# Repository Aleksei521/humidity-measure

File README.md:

# humidity-measure
Moisture and temperature meter on PSOC 4200 and segment LCD
https://habr.com/ru/post/547644/#habracut

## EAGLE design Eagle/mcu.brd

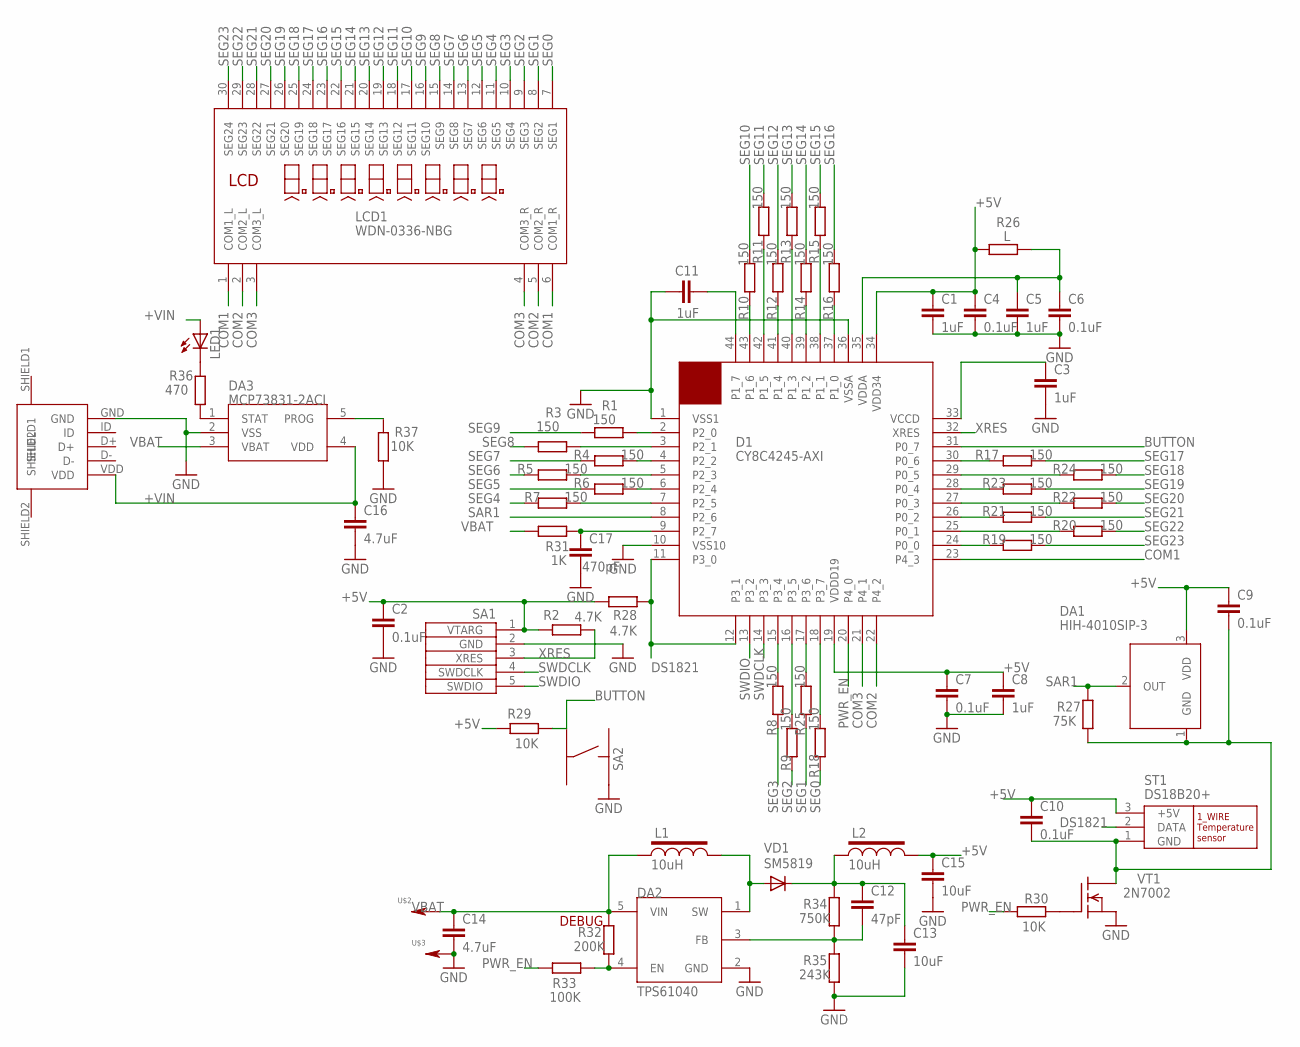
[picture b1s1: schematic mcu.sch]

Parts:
C1, C3, C5, C8, C11: 1uF; C0603
C2, C4, C6, C7, C9, C10: 0.1uF; C0603
C12: 47pF; C0805
C13, C15: 10uF; C0805
C14, C16: 4.7uF; C0805
C17: 470pF; C0603
D1: CY8C4245-AXI; TQFP44
DA1: HIH-4010SIP-3; SIP-3
DA2: TPS61040; SOT23-5L
DA3: MCP73831-2ACI; SOT23-5L
L1, L2: 10uH; SQC453226
LCD1: WDN-0336-NBG; WDN0336
LED1: LEDSMT1206; 1206
R1, R3, R4, R5, R6, R7, R8, R9, R10, R11, R12, R13, R14, R15, R16, R17, R18, R19, R20, R21, R22, R23, R24, R25: 150; R0603
R2, R28: 4.7K; R0603
R26: L; R0805
R27: 75K; R0603
R29, R30, R37: 10K; R0603
R31: 1K; R0603
R32: 200K; R0603
R33: 100K; R0603
R34: 750K; R0805
R35: 243K; R0805
R36: 470; R1206
SA1: SWDSWD-5; SWD-5
SA2: TACKT_BUTTONIIT-1102S; IIT-1102S
ST1: DS18B20+; TO92-
U$1: USB-MICRO; USB-MICRO-SMD
U$2: 1-PINHOME; 1-PIN_HOME
U$3: 1-PIN2_54; 1_PIN_2_54
VD1: SM5819; MELF-MLL41
VT1: 2N7002; SOT23

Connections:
+5V: C1.1, C2.1, C4.1, C7.1, C8.1, C9.1, C10.1, C15.1, D1.19 (VDDD19), D1.34 (VDD34), DA1.3 (VDD), L2.2 (L2), R2.2, R26.1, R28.2, R29.2, SA1.1 (VTARG), ST1.3 (+5V)
+VIN: C16.1, DA3.4 (VDD), LED1.A, U$1.VDD
BUTTON: D1.31 (P0_7), R29.1, SA2.SSR (2)
COM1: D1.23 (P4_3), LCD1.1 (COM1_L), LCD1.6 (COM1_R)
COM2: D1.22 (P4_2), LCD1.2 (COM2_L), LCD1.5 (COM2_R)
COM3: D1.21 (P4_1), LCD1.3 (COM3_L), LCD1.4 (COM3_R)
DS1821: D1.11 (P3_0), D1.12 (P3_1), R28.1, ST1.2 (DATA)
GND: C1.2, C2.2, C3.2, C4.2, C5.2, C6.2, C7.2, C8.2, C11.1, C13.2, C14.2, C15.2, C16.2, C17.2, D1.1 (VSS1), D1.10 (VSS10), D1.36 (VSSA), DA2.2 (GND), DA3.2 (VSS), R35.1, R37.1, SA1.2 (GND), SA2.SL (3), U$1.GND, U$3.P$1, VT1.2 (S)
unnamed: D1.2 (P2_0), R1.2
unnamed: D1.4 (P2_2), R4.2
unnamed: D1.6 (P2_4), R6.2
unnamed: D1.15 (P3_4), R8.2
unnamed: D1.3 (P2_1), R3.2
unnamed: D1.5 (P2_3), R5.2
unnamed: D1.7 (P2_5), R7.2
unnamed: D1.43 (P1_6), R10.1
unnamed: C3.1, D1.33 (VCCD)
unnamed: D1.42 (P1_5), R11.1
unnamed: D1.41 (P1_4), R12.1
unnamed: C5.1, C6.1, D1.35 (VDDA), R26.2
unnamed: D1.40 (P1_3), R13.1
unnamed: D1.39 (P1_2), R14.1
unnamed: D1.38 (P1_1), R15.1
unnamed: D1.37 (P1_0), R16.1
unnamed: D1.30 (P0_6), R17.1
unnamed: D1.29 (P0_5), R24.1
unnamed: D1.28 (P0_4), R23.1
unnamed: D1.16 (P3_5), R9.2
unnamed: D1.17 (P3_6), R25.2
unnamed: D1.18 (P3_7), R18.2
unnamed: D1.27 (P0_3), R22.1
unnamed: D1.26 (P0_2), R21.1
unnamed: D1.25 (P0_1), R20.1
unnamed: D1.24 (P0_0), R19.1
unnamed: C11.2, D1.44 (P1_7)
unnamed: C9.2, C10.2, DA1.1 (GND), R27.1, ST1.1 (GND), VT1.3 (D)
unnamed: R30.2, VT1.1 (G)
unnamed: C12.2, DA2.3 (FB), R34.1, R35.2
unnamed: DA2.4 (EN), R32.1, R33.2
unnamed: DA2.1 (SW), L1.2 (L2), VD1.A
unnamed: C12.1, C13.1, L2.1 (L1), R34.2, VD1.C
unnamed: DA3.1 (STAT), R36.1
unnamed: LED1.C, R36.2
unnamed: DA3.5 (PROG), R37.2
PWR_EN: D1.20 (P4_0), R30.1, R33.1
SAR1: D1.8 (P2_6), DA1.2 (OUT), R27.2
SAR2: C17.1, D1.9 (P2_7), R31.2
SEG0: LCD1.7 (SEG1), R18.1
SEG1: LCD1.8 (SEG2), R25.1
SEG2: LCD1.9 (SEG3), R9.1
SEG3: LCD1.10 (SEG4), R8.1
SEG4: LCD1.11 (SEG5), R7.1
SEG5: LCD1.12 (SEG6), R6.1
SEG6: LCD1.13 (SEG7), R5.1
SEG7: LCD1.14 (SEG8), R4.1
SEG8: LCD1.15 (SEG9), R3.1
SEG9: LCD1.16 (SEG10), R1.1
SEG10: LCD1.17 (SEG11), R10.2
SEG11: LCD1.18 (SEG12), R11.2
SEG12: LCD1.19 (SEG13), R12.2
SEG13: LCD1.20 (SEG14), R13.2
SEG14: LCD1.21 (SEG15), R14.2
SEG15: LCD1.22 (SEG16), R15.2
SEG16: LCD1.23 (SEG17), R16.2
SEG17: LCD1.24 (SEG18), R17.2
SEG18: LCD1.25 (SEG19), R24.2
SEG19: LCD1.26 (SEG20), R23.2
SEG20: LCD1.27 (SEG21), R22.2
SEG21: LCD1.28 (SEG22), R21.2
SEG22: LCD1.29 (SEG23), R20.2
SEG23: LCD1.30 (SEG24), R19.2
SWDCLK: D1.14 (P3_3), SA1.4 (SWDCLK)
SWDIO: D1.13 (P3_2), SA1.5 (SWDIO)
VBAT: C14.1, DA2.5 (VIN), DA3.3 (VBAT), L1.1 (L1), R31.1, R32.2, U$2.P$1
XRES: D1.32 (XRES), R2.1, SA1.3 (XRES)

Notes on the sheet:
DEBUG

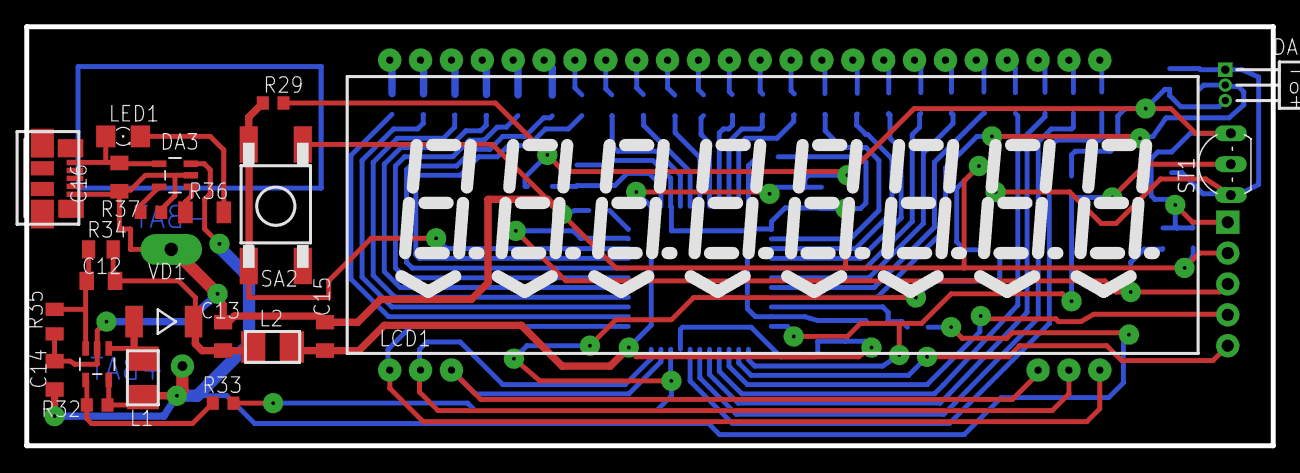
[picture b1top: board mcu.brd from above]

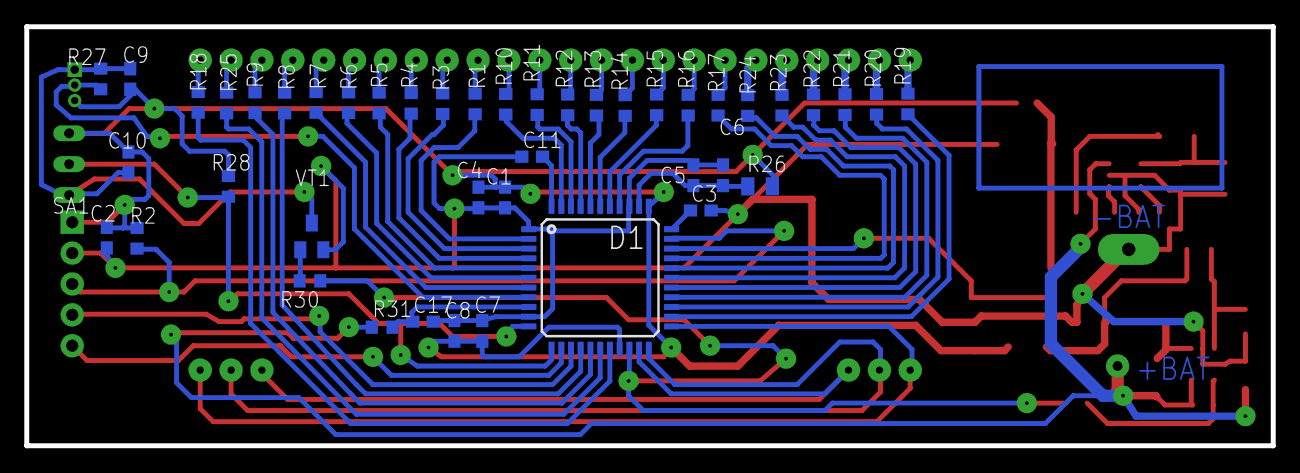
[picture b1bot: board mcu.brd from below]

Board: 2 copper layers, 102.5 x 34.5 mm, 70 parts (45 on the bottom side), 75 nets.

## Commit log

2021-03-17 posted on git
    posted on git
2021-03-18 added define for constants in contrast adjustment
2021-04-12 add url description
2024-01-22 Сделал усреднение измерения влажности по 64 отсчетам
